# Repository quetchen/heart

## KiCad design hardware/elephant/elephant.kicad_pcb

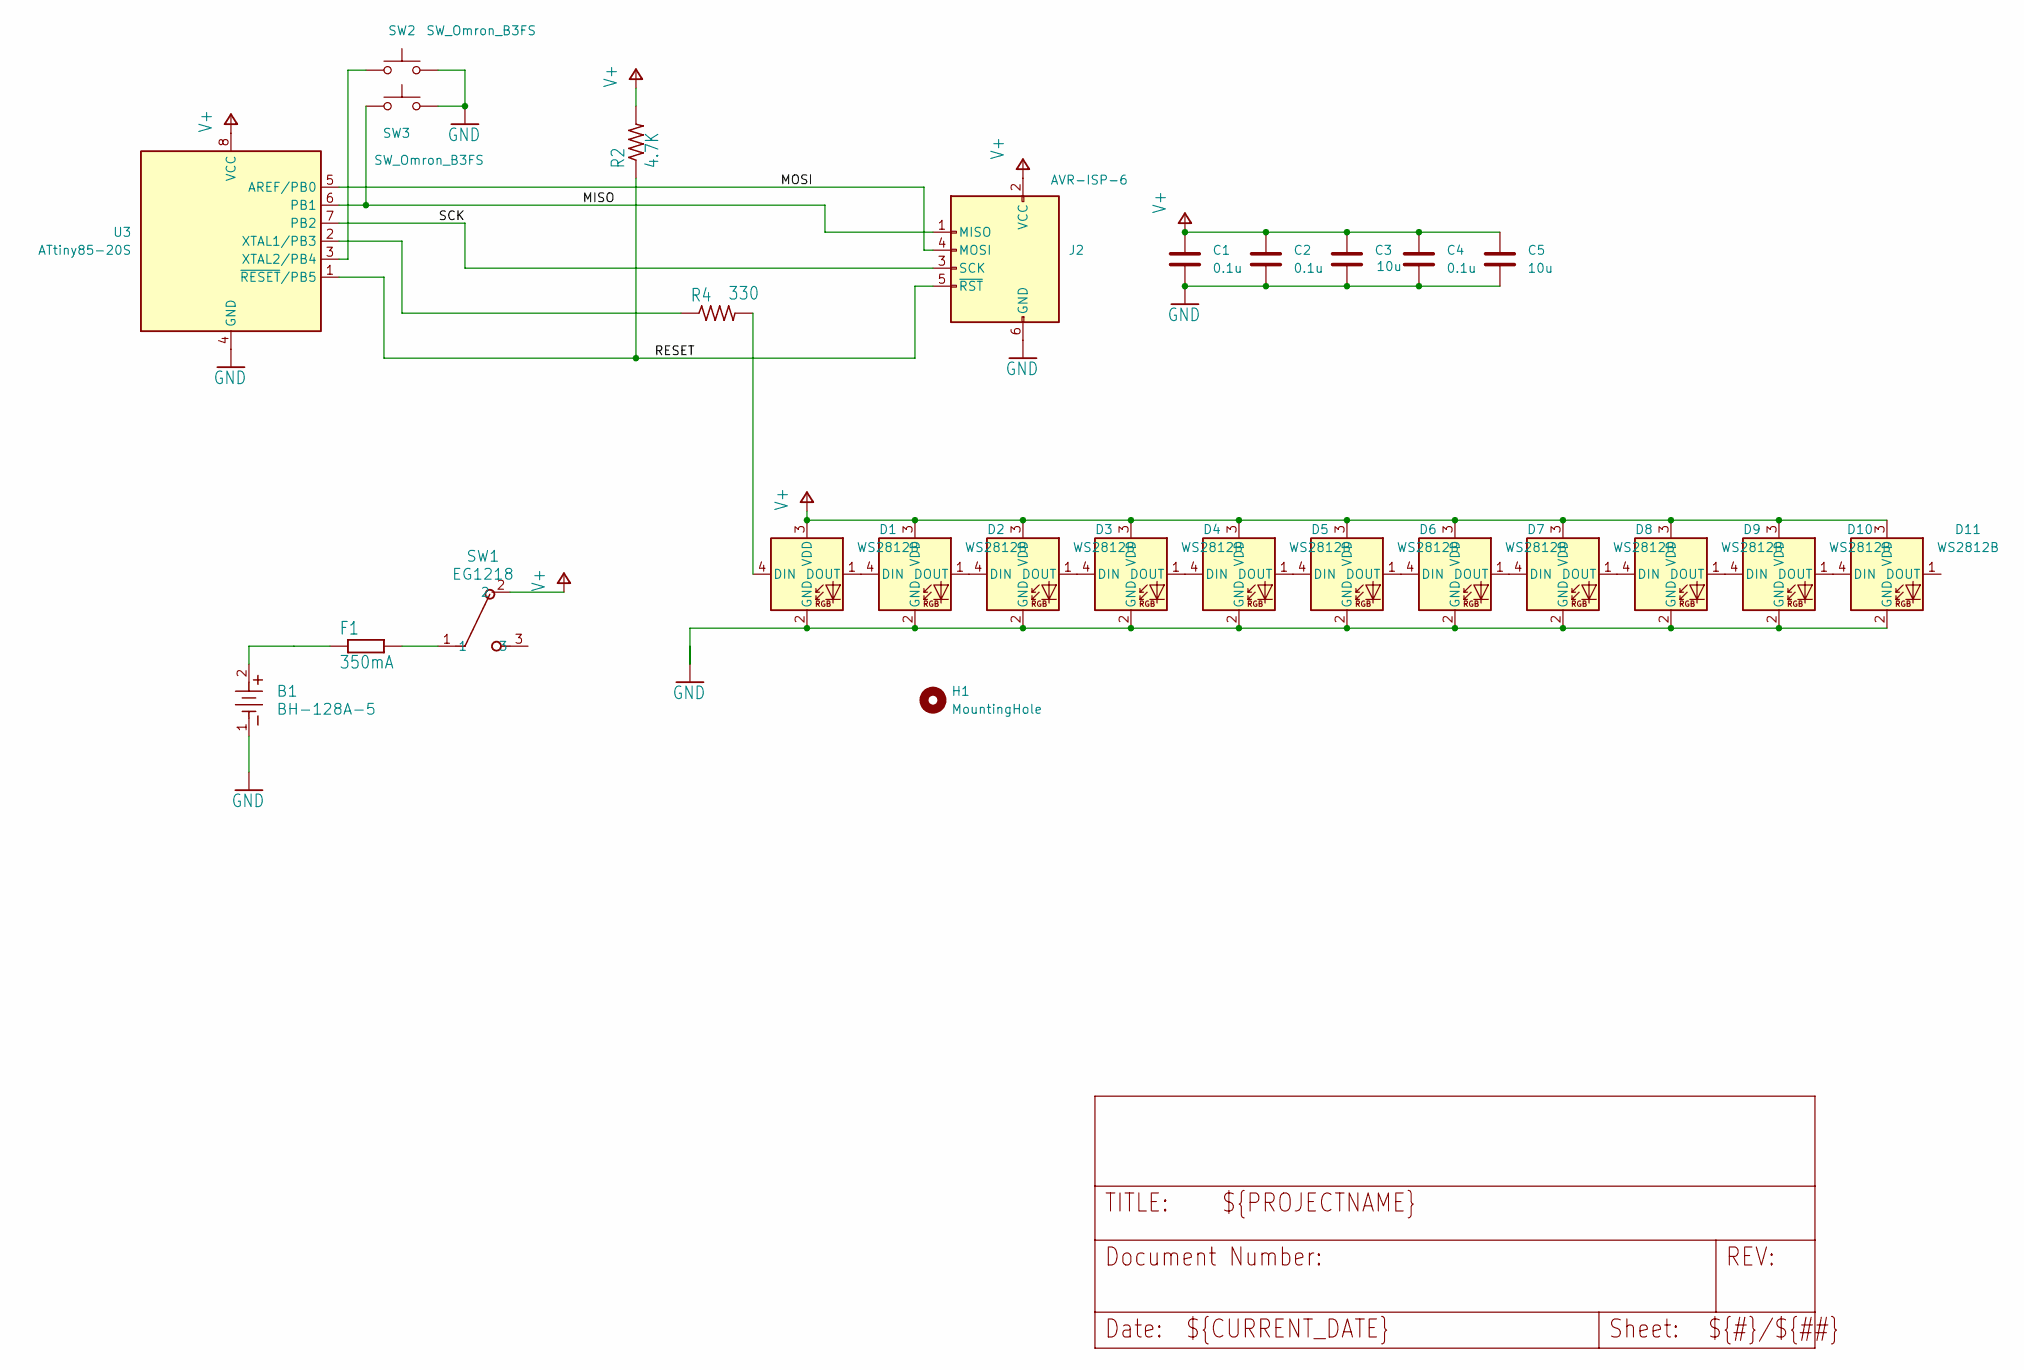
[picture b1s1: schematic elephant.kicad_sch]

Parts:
B1: BH-128A-5; BAT_BH-128A-5_ADM
C1, C2, C4: 0.1u; C_0603_1608Metric_Pad1.08x0.95mm_HandSolder
C3, C5: 10u; C_0603_1608Metric_Pad1.08x0.95mm_HandSolder
D1, D2, D3, D4, D5, D6, D7, D8, D9, D10, D11: WS2812B; LED_D5.0mm-4_RGB
F1: 350mA; R_0603_1608Metric_Pad0.98x0.95mm_HandSolder
H1: MountingHole; MountingHole_2.5mm
J2: AVR-ISP-6; IDC-Header_2x03_P2.54mm_Vertical
R2: 4.7K; R_0603_1608Metric_Pad0.98x0.95mm_HandSolder
R4: 330; R_0603_1608Metric_Pad0.98x0.95mm_HandSolder
SW1: EG1218; SW_1218_EWI
SW2, SW3: SW_Omron_B3FS; SW_SPST_Omron_B3FS-100xP
U3: ATtiny85-20S; SOIC-8W_5.3x5.3mm_P1.27mm

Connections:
/MISO: J2.1 (MISO), SW3.1, U3.6 (PB1)
/MOSI: J2.4 (MOSI), U3.5 (AREF/PB0)
/RESET: J2.5 (~RST), R2.1, U3.1 (~RESET/PB5)
/SCK: J2.3 (SCK), U3.7 (PB2)
GND: B1.1, C1.2, C2.2, C3.2, C4.2, C5.2, D1.2 (GND), D2.2 (GND), D3.2 (GND), D4.2 (GND), D5.2 (GND), D6.2 (GND), D7.2 (GND), D8.2 (GND), D9.2 (GND), D10.2 (GND), D11.2 (GND), J2.6 (GND), SW2.2, SW3.2, U3.4 (GND)
unnamed: B1.2, F1.1
unnamed: D1.4 (DIN), R4.2
unnamed: D1.1 (DOUT), D2.4 (DIN)
unnamed: D2.1 (DOUT), D3.4 (DIN)
unnamed: D3.1 (DOUT), D4.4 (DIN)
unnamed: D4.1 (DOUT), D5.4 (DIN)
unnamed: D5.1 (DOUT), D6.4 (DIN)
unnamed: D6.1 (DOUT), D7.4 (DIN)
unnamed: D7.1 (DOUT), D8.4 (DIN)
unnamed: D8.1 (DOUT), D9.4 (DIN)
unnamed: D9.1 (DOUT), D10.4 (DIN)
unnamed: D10.1 (DOUT), D11.4 (DIN)
unnamed: F1.2, SW1.1
unnamed: R4.1, U3.2 (XTAL1/PB3)
unnamed: SW2.1, U3.3 (XTAL2/PB4)
V+: C1.1, C2.1, C3.1, C4.1, C5.1, D1.3 (VDD), D2.3 (VDD), D3.3 (VDD), D4.3 (VDD), D5.3 (VDD), D6.3 (VDD), D7.3 (VDD), D8.3 (VDD), D9.3 (VDD), D10.3 (VDD), D11.3 (VDD), J2.2 (VCC), R2.2, SW1.2, U3.8 (VCC)

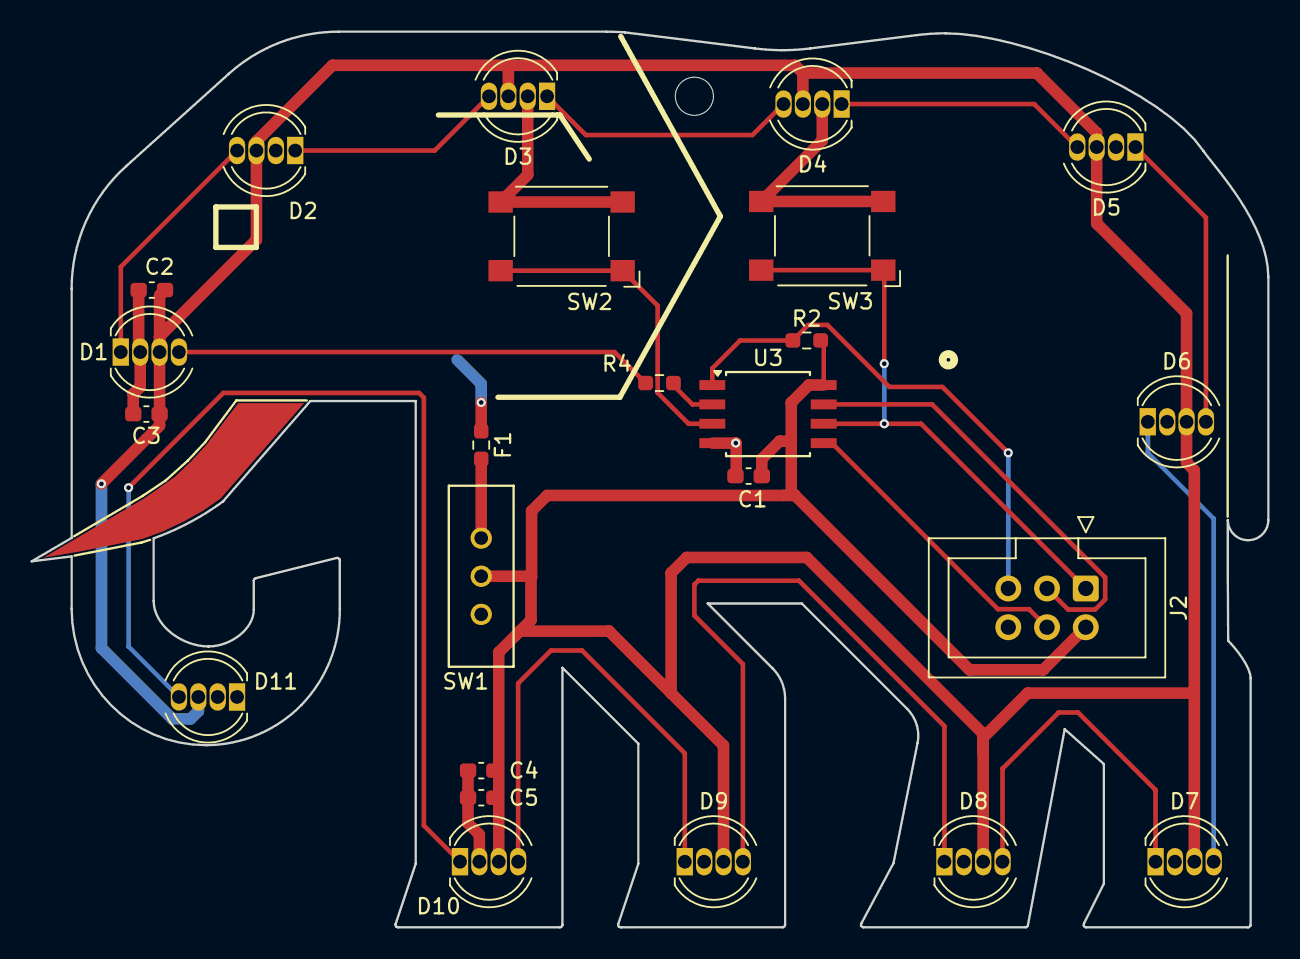
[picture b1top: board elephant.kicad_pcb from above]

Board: 2 copper layers, 81.1 x 58.7 mm, 26 parts (1 on the bottom side), 21 nets.

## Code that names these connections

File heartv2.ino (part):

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
//#define ELEPHANT

#define LED_PIN PIN_PB3
#define TOUCH_PIN1 PIN_PB4
#define TOUCH_PIN2 PIN_PB1

#define LED_POWER_ENABLE PIN_PB0

#ifdef ELEPHANT
#define BUTTON_PRESSED LOW
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  pinMode(TOUCH_PIN1, INPUT_PULLUP);
  pinMode(TOUCH_PIN2, INPUT_PULLUP);
  pinMode(SCK, INPUT);
  // for the elephant, PB0 is an input that gets grounded
  // when the charger is connected
  pinMode(PIN_PB0, INPUT_PULLUP);
#else
  pinMode(TOUCH_PIN1, INPUT);
  pinMode(TOUCH_PIN2, INPUT);
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
    if (!uvlo && (volt_rdg > UVLO_ENGAGE || EEPROM.read(EEPROM_UVLO)
#ifdef ELEPHANT
       || digitalRead(PIN_PB0)==LOW

#endif     
      )){
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
    } else if (uvlo && volt_rdg < UVLO_RELEASE
#ifdef ELEPHANT
      && digitalRead(PIN_PB0) == HIGH
#endif
    ){
      uvlo = false;
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
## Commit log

2024-12-16 Add files via upload
    Initial commit
2024-12-16 disable elephant target; add comment
2024-12-16 add hardware schematics
